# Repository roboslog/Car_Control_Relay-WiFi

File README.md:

# Car_Control_Relay-WiFi
 Car ignition control relay board

This Car ignition control relay board is very useful to control car to drive the relay with a 3.3v signal of esp8266. Relay connects & disconnects 12v supply of car battery to various components of bike. We have used LM2950 5V voltage regulator to drop down 12v DC supply to 5v DC supply. capacitor added on outer terminal to decrease the noise.

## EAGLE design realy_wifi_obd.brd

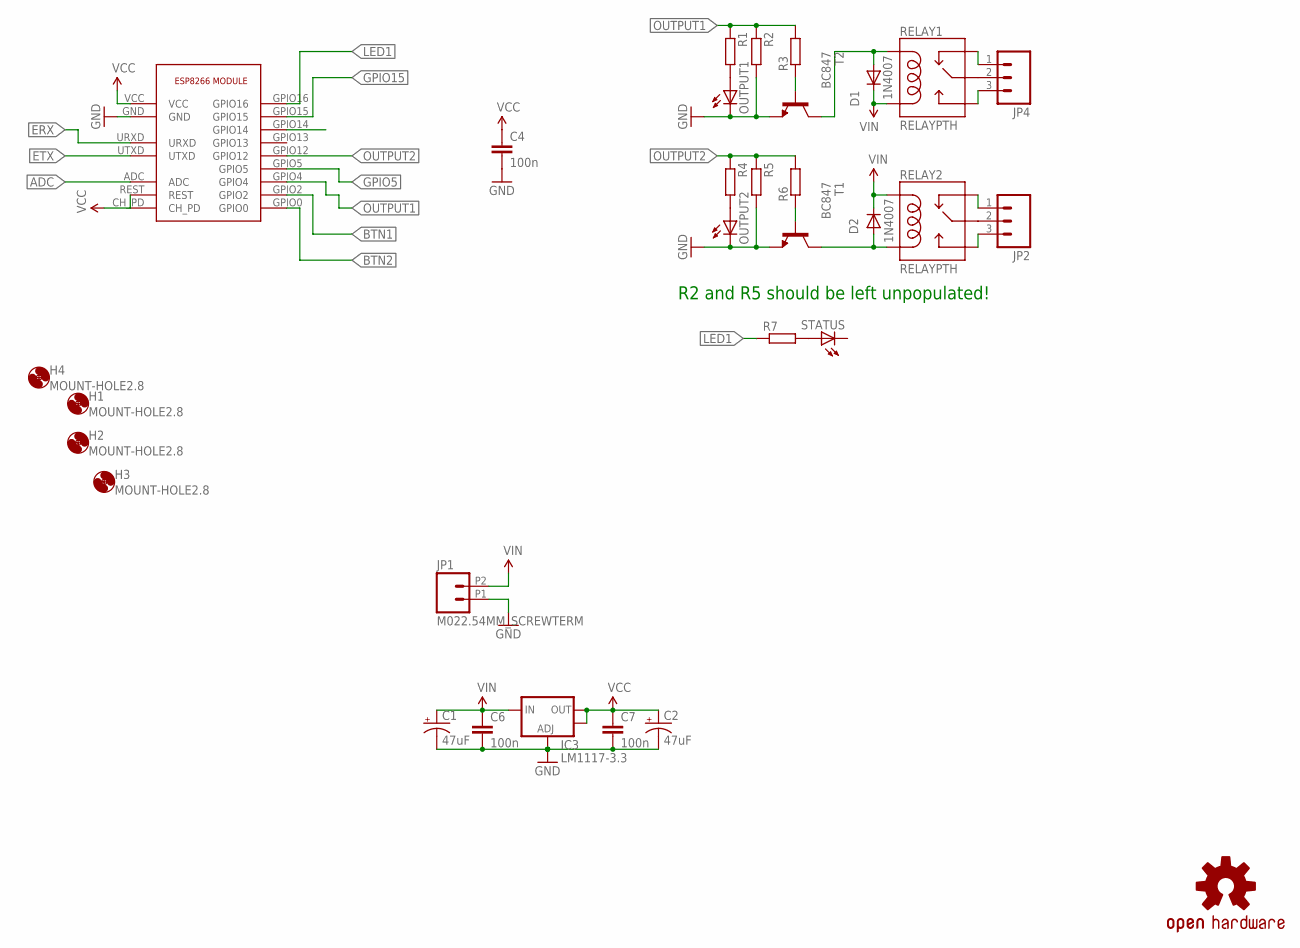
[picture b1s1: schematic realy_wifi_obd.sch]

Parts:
C1, C2: 47uF; PANASONIC_D
C4, C6, C7: 100n; C0805K
D1, D2: 1N4942; DO41-10
ESP8266: ESP8266ESP-07; ESP-12
H1, H2, H3, H4: MOUNT-HOLE2.8; 2,8
IC3: LM1117-3.3; SOT223
JP1: M022.54MM_SCREWTERM; 1X02_2.54_SCREWTERM
JP2, JP4: M03-SCREW-5MM; SCREWTERMINAL-5MM-3
LOGO1: OSHW-LOGOL; OSHW-LOGO-L
OUTPUT1, OUTPUT2: LEDCHIP-LED0805; CHIP-LED0805
R1, R2, R3, R4, R5, R6, R7: SMARTPRJ_R-EU_M0805; SMARTPRJ_M0805
RELAY1, RELAY2: RELAYPTH; SRD-05VDC-SL-C
STATUS: LEDCHIP-LED0805; CHIP-LED0805
T1, T2: BC847; SOT23

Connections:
ADC: ESP8266.ADC
BTN1: ESP8266.GPIO2
BTN2: ESP8266.GPIO0
DHT22: ESP8266.GPIO14
ERX: ESP8266.URXD
ETX: ESP8266.UTXD
GND: C1.-, C2.-, C4.2, C6.2, C7.2, ESP8266.GND, IC3.1 (ADJ), JP1.P1 (1), OUTPUT1.C, OUTPUT2.C, R2.2, R5.2, T1.2 (E), T2.2 (E)
GPIO5: ESP8266.GPIO5
GPIO15: ESP8266.GPIO15
LED1: ESP8266.GPIO16, R7.1
unnamed: D2.A, RELAY2.COIL0, T1.3 (C)
unnamed: D1.A, RELAY1.COIL1, T2.3 (C)
unnamed: JP2.2, RELAY2.SWCOMMON
unnamed: JP4.2, RELAY1.SWCOMMON
unnamed: JP4.1, RELAY1.SWCLOSED (SWCLOSE)
unnamed: JP4.3, RELAY1.SWOPEN
unnamed: JP2.3, RELAY2.SWOPEN
unnamed: JP2.1, RELAY2.SWCLOSED (SWCLOSE)
unnamed: R3.1, T2.1 (B)
unnamed: R6.1, T1.1 (B)
unnamed: OUTPUT2.A, R4.2
unnamed: R7.2, STATUS.A
unnamed: OUTPUT1.A, R1.2
OUTPUT1: ESP8266.GPIO4, R1.1, R2.1, R3.2
OUTPUT2: ESP8266.GPIO12, R4.1, R5.1, R6.2
VCC: C2.+, C4.1, C7.1, ESP8266.CH_PD, ESP8266.REST, ESP8266.VCC, IC3.2 (OUT), IC3.4 (OUT)
VIN: C1.+, C6.1, D1.C, D2.C, IC3.3 (IN), JP1.P2 (2), RELAY1.COIL0, RELAY2.COIL1

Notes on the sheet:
1N4007
R2 and R5 should be left unpopulated!

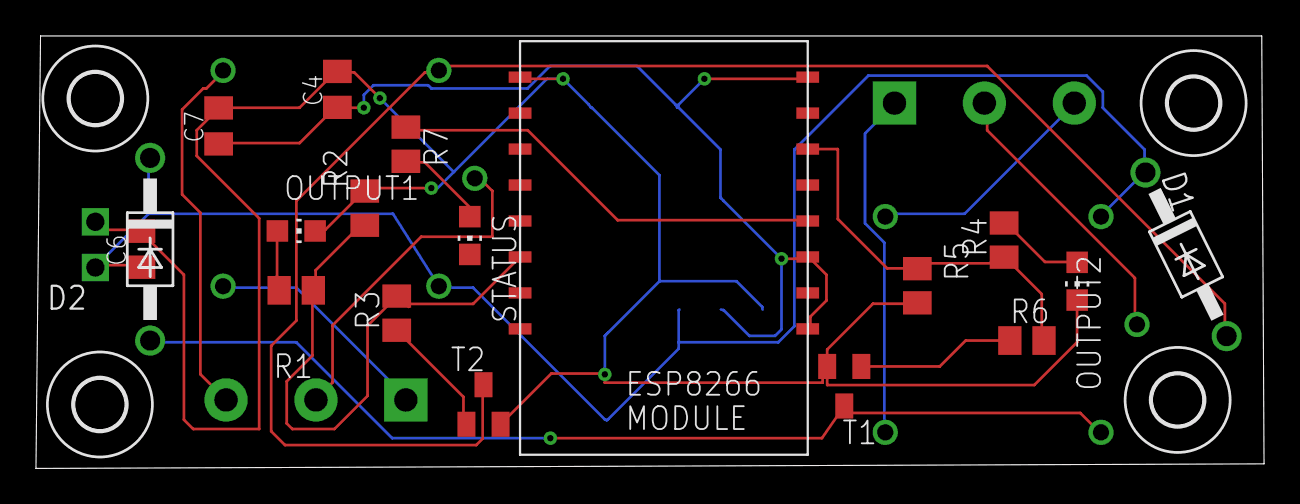
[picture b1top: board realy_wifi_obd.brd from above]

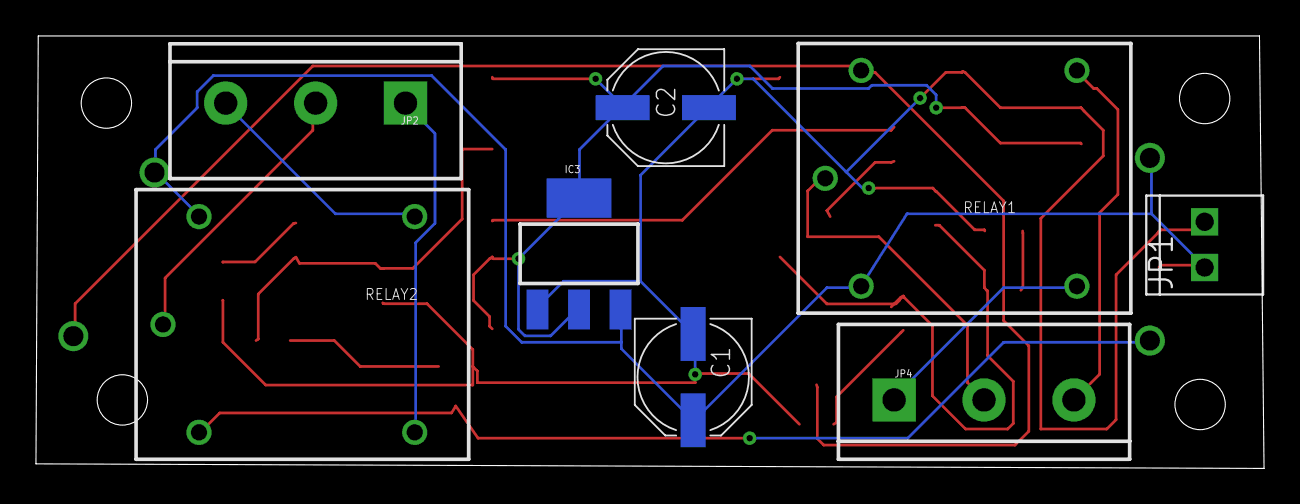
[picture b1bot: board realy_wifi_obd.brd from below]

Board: 2 copper layers, 68.3 x 24.1 mm, 31 parts (8 on the bottom side), 19 nets.

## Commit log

2020-05-20 Add files via upload
    realy_wifi_obd

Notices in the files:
parts and their libraries:
SparkFun-Capacitors: Licensing: Creative Commons ShareAlike 4.0 International - https://creativecommons.org/licenses/by-sa/4.0
